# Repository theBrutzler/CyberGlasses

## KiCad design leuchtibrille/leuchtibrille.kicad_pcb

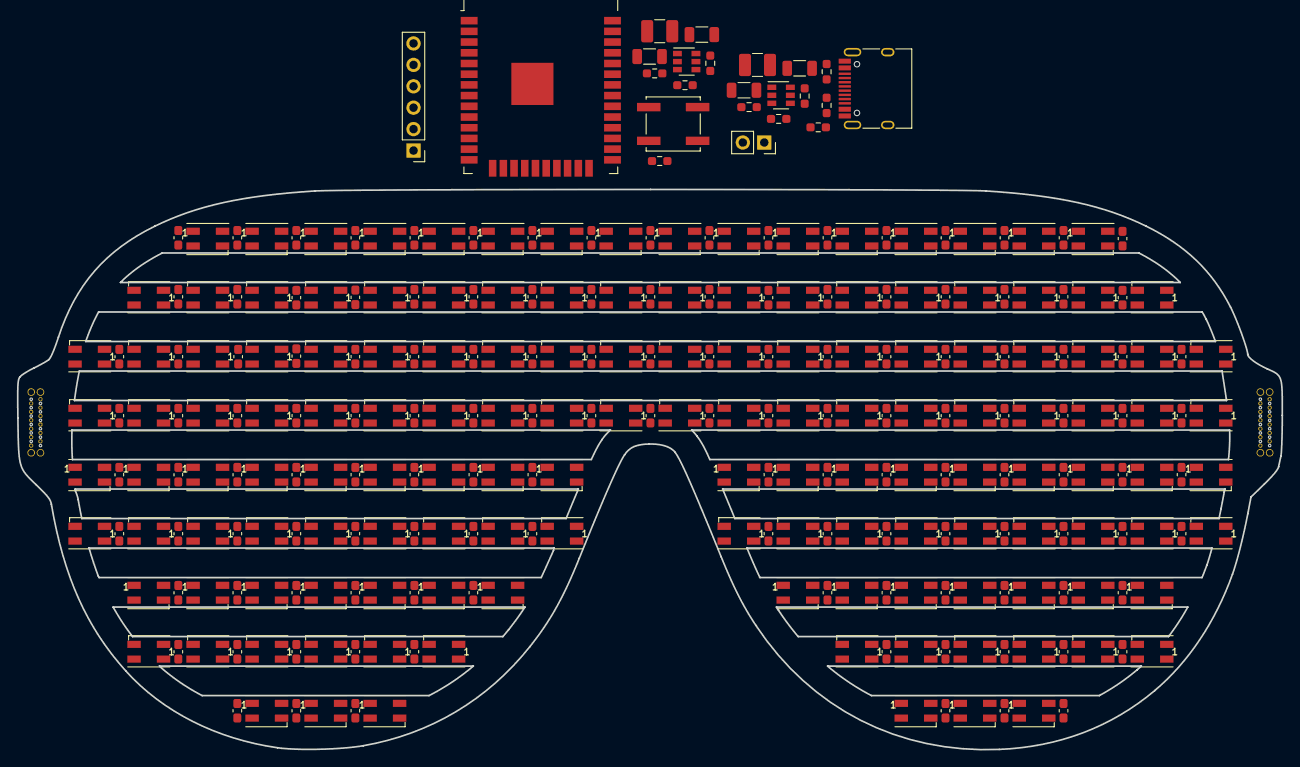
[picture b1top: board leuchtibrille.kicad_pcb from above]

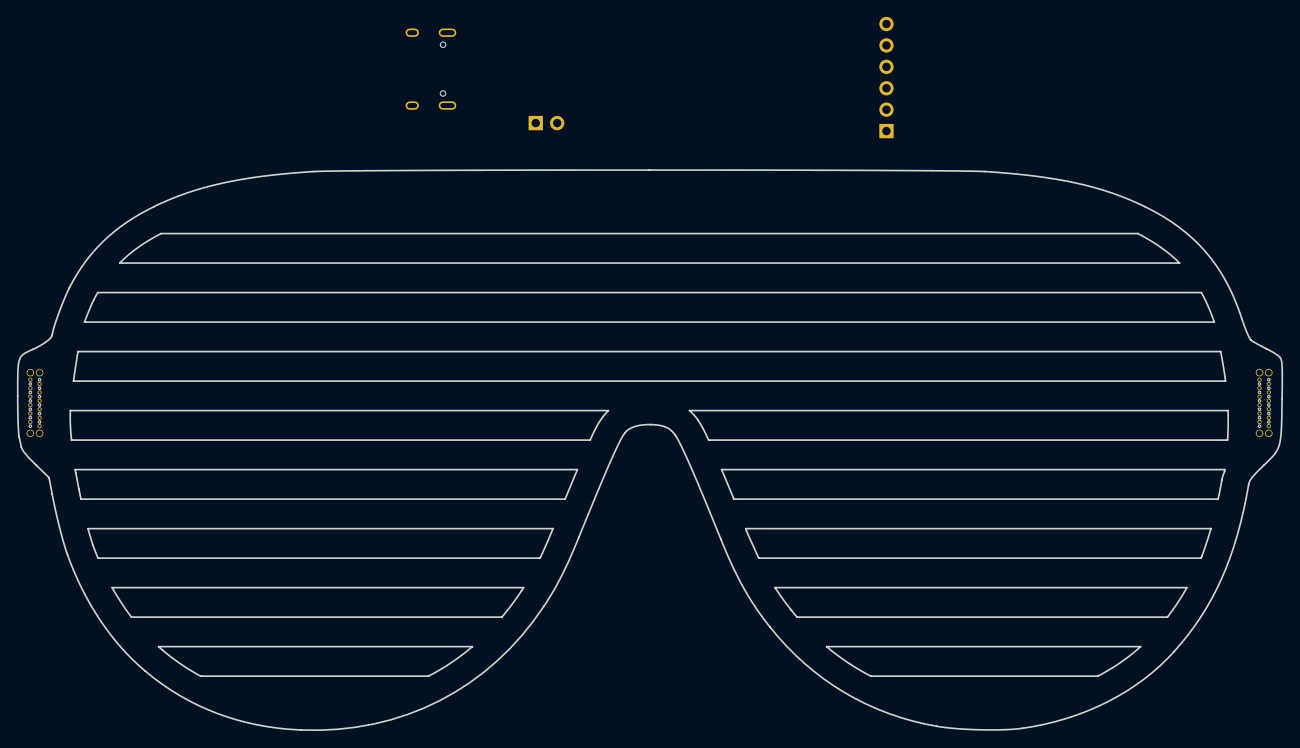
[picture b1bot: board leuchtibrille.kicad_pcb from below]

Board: 2 copper layers, 150.0 x 66.4 mm, 299 parts (2 on the bottom side), 160 nets, no tracks yet.

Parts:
C1, C2, C3, C4: 4µ7; C_1206_3216Metric
C8, C9, C10, C12, C13, C14, C15, C16, C17, C18, C19, C20, C21, C22, C23, C24, C25, C26, C27, C28, C29, C30, C31, C32, C33, C34, C35, C36, C37, C38, C39, C40, C41, C43, C44, C45, C47, C48, C49, C50, C51, C52, C53, C54, C55, C56, C57, C58, C59, C60, C61, C62, C63, C64, C65, C66, C67, C68, C69, C70, C71, C72, C73, C74, C75, C76, C78, C79, C80, C82, C83, C84, C85, C86, C87, C88, C89, C90, C91, C92, C93, C94, C95, C96, C97, C98, C99, C100, C101, C102, C103, C104, C105, C106, C107, C108, C109, C110, C111, C113, C114, C115, C117, C118, C119, C120, C121, C122, C123, C124, C125, C126, C127, C128, C129, C130, C131, C132, C133, C134, C135, C136, C137, C138, C139, C140, C141, C142, C143, C144, C145, C146: C100n; C_0603_1608Metric_Pad1.08x0.95mm_HandSolder
D1, D2, D3, D4, D5, D6, D7, D8, D9, D10, D11, D12, D13, D14, D15, D16, D17, D18, D19, D20, D21, D22, D23, D24, D25, D26, D27, D28, D29, D30, D31, D32, D33, D34, D35, D36, D37, D38, D39, D40, D41, D42, D43, D44, D45, D46, D47, D48, D49, D50, D51, D52, D53, D54, D55, D56, D57, D58, D59, D60, D61, D62, D63, D64, D65, D66, D67, D68, D69, D70, D71, D72, D73, D74, D75, D76, D77, D78, D79, D80, D81, D82, D83, D84, D85, D86, D87, D88, D89, D90, D91, D92, D93, D94, D95, D96, D97, D98, D99, D100, D101, D102, D103, D104, D105, D106, D107, D108, D109, D110, D111, D112, D113, D114, D115, D116, D117, D118, D119, D120, D121, D122, D123, D124, D125, D126, D127, D128, D129, D130, D131, D132, D133, D134, D135, D136, D137, D138, D139, D140, D141, D142: WS2812B; LED_SK6812MINI_PLCC4_3.5x3.5mm_P1.75mm
J1: Conn_01x06_Male; PinHeader_1x06_P2.54mm_Vertical
J2: Conn_01x02_Female; PinSocket_1x02_P2.54mm_Vertical
J3: USB_C_Receptacle_USB2.0; USB_C_Receptacle_HRO_TYPE-C-31-M-12
J4, J5: USB_C_Receptacle_USB2.0; USBC_THT
L1, L2: 2.2µ; L_1210_3225Metric_Pad1.42x2.65mm_HandSolder
R1, R2, R7, R8, R9, R10: 5K1; R_0603_1608Metric_Pad0.98x0.95mm_HandSolder
R3: 590K; R_0603_1608Metric_Pad0.98x0.95mm_HandSolder
R4, R6: 100K; R_0603_1608Metric_Pad0.98x0.95mm_HandSolder
R5: 430K; R_0603_1608Metric_Pad0.98x0.95mm_HandSolder
SW1: SW_Push; SW_Push_1P1T_NO_CK_KSC7xxJ
U1, U2: MT3420C; SOT-23-6
U3: ESP32-WROOM-32

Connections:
+3V3: C4.1, L2.2, R5.1, R7.1, U3.2 (VDD)
+5V: C1.1, J1.4, J3.A4 (VBUS), J3.A9 (VBUS), J3.B4 (VBUS), J3.B9 (VBUS), R1.2, U1.5 (IN)
+BATT: C2.1, C3.1, C8.1, C9.1, C10.1, C12.1, C13.1, C14.1, C15.1, C16.1, C17.1, C18.1, C19.1, C20.1, C21.1, C22.1, C23.1, C24.1, C25.1, C26.1, C27.1, C28.1, C29.1, C30.1, C31.1, C32.1, C33.1, C34.1, C35.1, C36.1, C37.1, C38.1, C39.1, C40.1, C41.1, C43.1, C44.1, C45.1, C47.1, C48.1, C49.1, C50.1, C51.1, C52.1, C53.1, C54.1, C55.1, C56.1, C57.1, C58.1, C59.1, C60.1, C61.1, C62.1, C63.1, C64.1, C65.1, C66.1, C67.1, C68.1, C69.1, C70.1, C71.1, C72.1, C73.1, C74.1, C75.1, C76.1, C78.1, C79.1, C80.1, C82.1, C83.1, C84.1, C85.1, C86.1, C87.1, C88.1, C89.1, C90.1, C91.1, C92.1, C93.1, C94.1, C95.1, C96.1, C97.1, C98.1, C99.1, C100.1, C101.1, C102.1, C103.1, C104.1, C105.1, C106.1, C107.1, C108.1, C109.1, C110.1, C111.1, C113.1, C114.1, C115.1, C117.1, C118.1, C119.1, C120.1, C121.1, C122.1, C123.1, C124.1, C125.1, C126.1, C127.1, C128.1, C129.1, C130.1, C131.1, C132.1, C133.1, C134.1, C135.1, C136.1, C137.1, C138.1, C139.1, C140.1, C141.1, C142.1, C143.1, C144.1, C145.1, C146.1, D1.1 (VDD), D2.1 (VDD), D3.1 (VDD), D4.1 (VDD), D5.1 (VDD), D6.1 (VDD), D7.1 (VDD), D8.1 (VDD), D9.1 (VDD), D10.1 (VDD), D11.1 (VDD), D12.1 (VDD), D13.1 (VDD), D14.1 (VDD), D15.1 (VDD), D16.1 (VDD), D17.1 (VDD), D18.1 (VDD), D19.1 (VDD), D20.1 (VDD), D21.1 (VDD), D22.1 (VDD), D23.1 (VDD), D24.1 (VDD), D25.1 (VDD), D26.1 (VDD), D27.1 (VDD), D28.1 (VDD), D29.1 (VDD), D30.1 (VDD), D31.1 (VDD), D32.1 (VDD), D33.1 (VDD), D34.1 (VDD), D35.1 (VDD), D36.1 (VDD), D37.1 (VDD), D38.1 (VDD), D39.1 (VDD), D40.1 (VDD), D41.1 (VDD), D42.1 (VDD), D43.1 (VDD), D44.1 (VDD), D45.1 (VDD), D46.1 (VDD), D47.1 (VDD), D48.1 (VDD), D49.1 (VDD), D50.1 (VDD), D51.1 (VDD), D52.1 (VDD), D53.1 (VDD), D54.1 (VDD), D55.1 (VDD), D56.1 (VDD), D57.1 (VDD), D58.1 (VDD), D59.1 (VDD), D60.1 (VDD), D61.1 (VDD), D62.1 (VDD), D63.1 (VDD), D64.1 (VDD), D65.1 (VDD), D66.1 (VDD), D67.1 (VDD), D68.1 (VDD), D69.1 (VDD), D70.1 (VDD), D71.1 (VDD), D72.1 (VDD), D73.1 (VDD), D74.1 (VDD), D75.1 (VDD), D76.1 (VDD), D77.1 (VDD), D78.1 (VDD), D79.1 (VDD), D80.1 (VDD), D81.1 (VDD), D82.1 (VDD), D83.1 (VDD), D84.1 (VDD), D85.1 (VDD), D86.1 (VDD), D87.1 (VDD), D88.1 (VDD), D89.1 (VDD), D90.1 (VDD), D91.1 (VDD), D92.1 (VDD), D93.1 (VDD), D94.1 (VDD), D95.1 (VDD), D96.1 (VDD), D97.1 (VDD), D98.1 (VDD), D99.1 (VDD), D100.1 (VDD), D101.1 (VDD), D102.1 (VDD), D103.1 (VDD), D104.1 (VDD), D105.1 (VDD), D106.1 (VDD), D107.1 (VDD), D108.1 (VDD), D109.1 (VDD), D110.1 (VDD), D111.1 (VDD), D112.1 (VDD), D113.1 (VDD), D114.1 (VDD), D115.1 (VDD), D116.1 (VDD), D117.1 (VDD), D118.1 (VDD), D119.1 (VDD), D120.1 (VDD), D121.1 (VDD), D122.1 (VDD), D123.1 (VDD), D124.1 (VDD), D125.1 (VDD), D126.1 (VDD), D127.1 (VDD), D128.1 (VDD), D129.1 (VDD), D130.1 (VDD), D131.1 (VDD), D132.1 (VDD), D133.1 (VDD), D134.1 (VDD), D135.1 (VDD), D136.1 (VDD), D137.1 (VDD), D138.1 (VDD), D139.1 (VDD), D140.1 (VDD), D141.1 (VDD), D142.1 (VDD), J2.2, J4.A9 (VBUS), J4.B4 (VBUS), J5.A4 (VBUS), J5.A9 (VBUS), L1.2, R2.2, R3.1, U2.5 (IN)
/ENABLE: J1.6, U3.3 (EN)
/gschau/DIN: D3.4 (DIN), J5.A6 (D+), J5.A7 (D-)
/gschau/DOUT: D22.2 (DOUT), D38.4 (DIN)
/sheet60A4741D/DOUT: D92.2 (DOUT), D108.4 (DIN)
/sheet60A47726/DOUT: D1.4 (DIN), D127.2 (DOUT)
/sheet60813E03/DOUT: D57.2 (DOUT), D73.4 (DIN)
GND: C1.2, C2.2, C3.2, C4.2, C8.2, C9.2, C10.2, C12.2, C13.2, C14.2, C15.2, C16.2, C17.2, C18.2, C19.2, C20.2, C21.2, C22.2, C23.2, C24.2, C25.2, C26.2, C27.2, C28.2, C29.2, C30.2, C31.2, C32.2, C33.2, C34.2, C35.2, C36.2, C37.2, C38.2, C39.2, C40.2, C41.2, C43.2, C44.2, C45.2, C47.2, C48.2, C49.2, C50.2, C51.2, C52.2, C53.2, C54.2, C55.2, C56.2, C57.2, C58.2, C59.2, C60.2, C61.2, C62.2, C63.2, C64.2, C65.2, C66.2, C67.2, C68.2, C69.2, C70.2, C71.2, C72.2, C73.2, C74.2, C75.2, C76.2, C78.2, C79.2, C80.2, C82.2, C83.2, C84.2, C85.2, C86.2, C87.2, C88.2, C89.2, C90.2, C91.2, C92.2, C93.2, C94.2, C95.2, C96.2, C97.2, C98.2, C99.2, C100.2, C101.2, C102.2, C103.2, C104.2, C105.2, C106.2, C107.2, C108.2, C109.2, C110.2, C111.2, C113.2, C114.2, C115.2, C117.2, C118.2, C119.2, C120.2, C121.2, C122.2, C123.2, C124.2, C125.2, C126.2, C127.2, C128.2, C129.2, C130.2, C131.2, C132.2, C133.2, C134.2, C135.2, C136.2, C137.2, C138.2, C139.2, C140.2, C141.2, C142.2, C143.2, C144.2, C145.2, C146.2, D1.3 (VSS), D2.3 (VSS), D3.3 (VSS), D4.3 (VSS), D5.3 (VSS), D6.3 (VSS), D7.3 (VSS), D8.3 (VSS), D9.3 (VSS), D10.3 (VSS), D11.3 (VSS), D12.3 (VSS), D13.3 (VSS), D14.3 (VSS), D15.3 (VSS), D16.3 (VSS), D17.3 (VSS), D18.3 (VSS), D19.3 (VSS), D20.3 (VSS), D21.3 (VSS), D22.3 (VSS), D23.3 (VSS), D24.3 (VSS), D25.3 (VSS), D26.3 (VSS), D27.3 (VSS), D28.3 (VSS), D29.3 (VSS), D30.3 (VSS), D31.3 (VSS), D32.3 (VSS), D33.3 (VSS), D34.3 (VSS), D35.3 (VSS), D36.3 (VSS), D37.3 (VSS), D38.3 (VSS), D39.3 (VSS), D40.3 (VSS), D41.3 (VSS), D42.3 (VSS), D43.3 (VSS), D44.3 (VSS), D45.3 (VSS), D46.3 (VSS), D47.3 (VSS), D48.3 (VSS), D49.3 (VSS), D50.3 (VSS), D51.3 (VSS), D52.3 (VSS), D53.3 (VSS), D54.3 (VSS), D55.3 (VSS), D56.3 (VSS), D57.3 (VSS), D58.3 (VSS), D59.3 (VSS), D60.3 (VSS), D61.3 (VSS), D62.3 (VSS), D63.3 (VSS), D64.3 (VSS), D65.3 (VSS), D66.3 (VSS), D67.3 (VSS), D68.3 (VSS), D69.3 (VSS), D70.3 (VSS), D71.3 (VSS), D72.3 (VSS), D73.3 (VSS), D74.3 (VSS), D75.3 (VSS), D76.3 (VSS), D77.3 (VSS), D78.3 (VSS), D79.3 (VSS), D80.3 (VSS), D81.3 (VSS), D82.3 (VSS), D83.3 (VSS), D84.3 (VSS), D85.3 (VSS), D86.3 (VSS), D87.3 (VSS), D88.3 (VSS), D89.3 (VSS), D90.3 (VSS), D91.3 (VSS), D92.3 (VSS), D93.3 (VSS), D94.3 (VSS), D95.3 (VSS), D96.3 (VSS), D97.3 (VSS), D98.3 (VSS), D99.3 (VSS), D100.3 (VSS), D101.3 (VSS), D102.3 (VSS), D103.3 (VSS), D104.3 (VSS), D105.3 (VSS), D106.3 (VSS), D107.3 (VSS), D108.3 (VSS), D109.3 (VSS), D110.3 (VSS), D111.3 (VSS), D112.3 (VSS), D113.3 (VSS), D114.3 (VSS), D115.3 (VSS), D116.3 (VSS), D117.3 (VSS), D118.3 (VSS), D119.3 (VSS), D120.3 (VSS), D121.3 (VSS), D122.3 (VSS), D123.3 (VSS), D124.3 (VSS), D125.3 (VSS), D126.3 (VSS), D127.3 (VSS), D128.3 (VSS), D129.3 (VSS), D130.3 (VSS), D131.3 (VSS), D132.3 (VSS), D133.3 (VSS), D134.3 (VSS), D135.3 (VSS), D136.3 (VSS), D137.3 (VSS), D138.3 (VSS), D139.3 (VSS), D140.3 (VSS), D141.3 (VSS), D142.3 (VSS), J1.1, J2.1, J3.A1 (GND), J3.A12 (GND), J3.B1 (GND), J3.B12 (GND), J3.S1 (SHIELD), J4.A1 (GND), J4.B12 (GND), J4.S1 (SHIELD), J5.A12 (GND), J5.B12 (GND), J5.S1 (SHIELD), R4.2, R6.2, R8.1, R9.1, SW1.2, U1.2 (GND), U2.2 (GND), U3.1 (GND), U3.15 (GND), U3.38 (GND), U3.39 (GND)
unnamed: D1.2 (DOUT), D2.4 (DIN)
unnamed: D3.2 (DOUT), D7.4 (DIN)
unnamed: D4.2 (DOUT), D8.4 (DIN)
unnamed: D5.2 (DOUT), D9.4 (DIN)
unnamed: D10.2 (DOUT), D14.4 (DIN)
unnamed: D6.2 (DOUT), D10.4 (DIN)
unnamed: D11.2 (DOUT), D15.4 (DIN)
unnamed: D7.2 (DOUT), D11.4 (DIN)
unnamed: D12.2 (DOUT), D16.4 (DIN)
unnamed: D8.2 (DOUT), D12.4 (DIN)
unnamed: D13.2 (DOUT), D17.4 (DIN)
unnamed: D9.2 (DOUT), D13.4 (DIN)
unnamed: D14.2 (DOUT), D18.4 (DIN)
unnamed: D15.2 (DOUT), D19.4 (DIN)
unnamed: D16.2 (DOUT), D20.4 (DIN)
unnamed: D17.2 (DOUT), D21.4 (DIN)
unnamed: D18.2 (DOUT), D22.4 (DIN)
unnamed: D19.2 (DOUT), D23.4 (DIN)
unnamed: D20.2 (DOUT), D24.4 (DIN)
unnamed: D21.2 (DOUT), D25.4 (DIN)
unnamed: D23.2 (DOUT), D26.4 (DIN)
unnamed: D24.2 (DOUT), D27.4 (DIN)
unnamed: D25.2 (DOUT), D28.4 (DIN)
unnamed: D26.2 (DOUT), D29.4 (DIN)
unnamed: D27.2 (DOUT), D30.4 (DIN)
unnamed: D28.2 (DOUT), D31.4 (DIN)
unnamed: D29.2 (DOUT), D32.4 (DIN)
unnamed: D30.2 (DOUT), D33.4 (DIN)
unnamed: D31.2 (DOUT), D34.4 (DIN)
unnamed: D32.2 (DOUT), D35.4 (DIN)
unnamed: D33.2 (DOUT), D36.4 (DIN)
unnamed: D34.2 (DOUT), D37.4 (DIN)
unnamed: D4.4 (DIN), D35.2 (DOUT)
unnamed: D5.4 (DIN), D36.2 (DOUT)
unnamed: D6.4 (DIN), D37.2 (DOUT)
unnamed: D38.2 (DOUT), D42.4 (DIN)
unnamed: D39.2 (DOUT), D43.4 (DIN)
unnamed: D39.4 (DIN), D70.2 (DOUT)
unnamed: D40.2 (DOUT), D44.4 (DIN)
unnamed: D40.4 (DIN), D71.2 (DOUT)
unnamed: D41.2 (DOUT), D45.4 (DIN)
unnamed: D41.4 (DIN), D72.2 (DOUT)
unnamed: D42.2 (DOUT), D46.4 (DIN)
unnamed: D43.2 (DOUT), D47.4 (DIN)
unnamed: D44.2 (DOUT), D48.4 (DIN)
unnamed: D45.2 (DOUT), D49.4 (DIN)
unnamed: D46.2 (DOUT), D50.4 (DIN)
unnamed: D47.2 (DOUT), D51.4 (DIN)
unnamed: D48.2 (DOUT), D52.4 (DIN)
unnamed: D49.2 (DOUT), D53.4 (DIN)
unnamed: D50.2 (DOUT), D54.4 (DIN)
unnamed: D51.2 (DOUT), D55.4 (DIN)
unnamed: D52.2 (DOUT), D56.4 (DIN)
unnamed: D53.2 (DOUT), D57.4 (DIN)
unnamed: D54.2 (DOUT), D58.4 (DIN)
unnamed: D55.2 (DOUT), D59.4 (DIN)
unnamed: D56.2 (DOUT), D60.4 (DIN)
unnamed: D58.2 (DOUT), D61.4 (DIN)
unnamed: D59.2 (DOUT), D62.4 (DIN)
unnamed: D60.2 (DOUT), D63.4 (DIN)
unnamed: D61.2 (DOUT), D64.4 (DIN)
unnamed: D62.2 (DOUT), D65.4 (DIN)
unnamed: D63.2 (DOUT), D66.4 (DIN)
unnamed: D64.2 (DOUT), D67.4 (DIN)
unnamed: D65.2 (DOUT), D68.4 (DIN)
unnamed: D66.2 (DOUT), D69.4 (DIN)
unnamed: D67.2 (DOUT), D70.4 (DIN)
unnamed: D68.2 (DOUT), D71.4 (DIN)
unnamed: D69.2 (DOUT), D72.4 (DIN)
unnamed: D73.2 (DOUT), D77.4 (DIN)
unnamed: D74.2 (DOUT), D78.4 (DIN)
unnamed: D75.2 (DOUT), D79.4 (DIN)
unnamed: D76.2 (DOUT), D80.4 (DIN)
unnamed: D77.2 (DOUT), D81.4 (DIN)
unnamed: D78.2 (DOUT), D82.4 (DIN)
unnamed: D79.2 (DOUT), D83.4 (DIN)
unnamed: D80.2 (DOUT), D84.4 (DIN)
unnamed: D81.2 (DOUT), D85.4 (DIN)
unnamed: D82.2 (DOUT), D86.4 (DIN)
unnamed: D83.2 (DOUT), D87.4 (DIN)
unnamed: D84.2 (DOUT), D88.4 (DIN)
unnamed: D85.2 (DOUT), D89.4 (DIN)
unnamed: D86.2 (DOUT), D90.4 (DIN)
unnamed: D87.2 (DOUT), D91.4 (DIN)
unnamed: D88.2 (DOUT), D92.4 (DIN)
unnamed: D89.2 (DOUT), D93.4 (DIN)
unnamed: D90.2 (DOUT), D94.4 (DIN)
unnamed: D91.2 (DOUT), D95.4 (DIN)
unnamed: D93.2 (DOUT), D96.4 (DIN)
unnamed: D94.2 (DOUT), D97.4 (DIN)
unnamed: D95.2 (DOUT), D98.4 (DIN)
unnamed: D96.2 (DOUT), D99.4 (DIN)
unnamed: D100.2 (DOUT), D103.4 (DIN)
unnamed: D97.2 (DOUT), D100.4 (DIN)
unnamed: D101.2 (DOUT), D104.4 (DIN)
unnamed: D98.2 (DOUT), D101.4 (DIN)
unnamed: D102.2 (DOUT), D105.4 (DIN)
unnamed: D99.2 (DOUT), D102.4 (DIN)
unnamed: D103.2 (DOUT), D106.4 (DIN)
unnamed: D104.2 (DOUT), D107.4 (DIN)
unnamed: D74.4 (DIN), D105.2 (DOUT)
unnamed: D75.4 (DIN), D106.2 (DOUT)
unnamed: D76.4 (DIN), D107.2 (DOUT)
unnamed: D108.2 (DOUT), D112.4 (DIN)
unnamed: D109.2 (DOUT), D113.4 (DIN)
unnamed: D109.4 (DIN), D140.2 (DOUT)
unnamed: D110.2 (DOUT), D114.4 (DIN)
unnamed: D110.4 (DIN), D141.2 (DOUT)
unnamed: D111.2 (DOUT), D115.4 (DIN)
unnamed: D111.4 (DIN), D142.2 (DOUT)
unnamed: D112.2 (DOUT), D116.4 (DIN)
unnamed: D113.2 (DOUT), D117.4 (DIN)
unnamed: D114.2 (DOUT), D118.4 (DIN)
unnamed: D115.2 (DOUT), D119.4 (DIN)
unnamed: D116.2 (DOUT), D120.4 (DIN)
unnamed: D117.2 (DOUT), D121.4 (DIN)
unnamed: D118.2 (DOUT), D122.4 (DIN)
unnamed: D119.2 (DOUT), D123.4 (DIN)
unnamed: D120.2 (DOUT), D124.4 (DIN)
unnamed: D121.2 (DOUT), D125.4 (DIN)
unnamed: D122.2 (DOUT), D126.4 (DIN)
unnamed: D123.2 (DOUT), D127.4 (DIN)
unnamed: D124.2 (DOUT), D128.4 (DIN)
unnamed: D125.2 (DOUT), D129.4 (DIN)
unnamed: D126.2 (DOUT), D130.4 (DIN)
unnamed: D128.2 (DOUT), D131.4 (DIN)
unnamed: D129.2 (DOUT), D132.4 (DIN)
unnamed: D130.2 (DOUT), D133.4 (DIN)
unnamed: D131.2 (DOUT), D134.4 (DIN)
unnamed: D132.2 (DOUT), D135.4 (DIN)
unnamed: D133.2 (DOUT), D136.4 (DIN)
unnamed: D134.2 (DOUT), D137.4 (DIN)
unnamed: D135.2 (DOUT), D138.4 (DIN)
unnamed: D136.2 (DOUT), D139.4 (DIN)
unnamed: D137.2 (DOUT), D140.4 (DIN)
unnamed: D138.2 (DOUT), D141.4 (DIN)
unnamed: D139.2 (DOUT), D142.4 (DIN)
unnamed: J1.2, U3.34 (RXD0/IO3)
unnamed: J1.3, U3.35 (TXD0/IO1)
unnamed: J1.5, R7.2, SW1.1, U3.25 (IO0)
unnamed: J3.A5 (CC1), R8.2
unnamed: J3.A6 (D+), R10.2
unnamed: J3.B5 (CC2), R9.2
unnamed: L1.1, U1.1 (SW)
unnamed: L2.1, U2.1 (SW)
unnamed: R1.1, U1.4 (EN)
unnamed: R2.1, U2.4 (EN)
unnamed: R3.2, R4.1, U1.3 (FB)
unnamed: R5.2, R6.1, U2.3 (FB)
unnamed: R10.1, U3.24 (IO2)

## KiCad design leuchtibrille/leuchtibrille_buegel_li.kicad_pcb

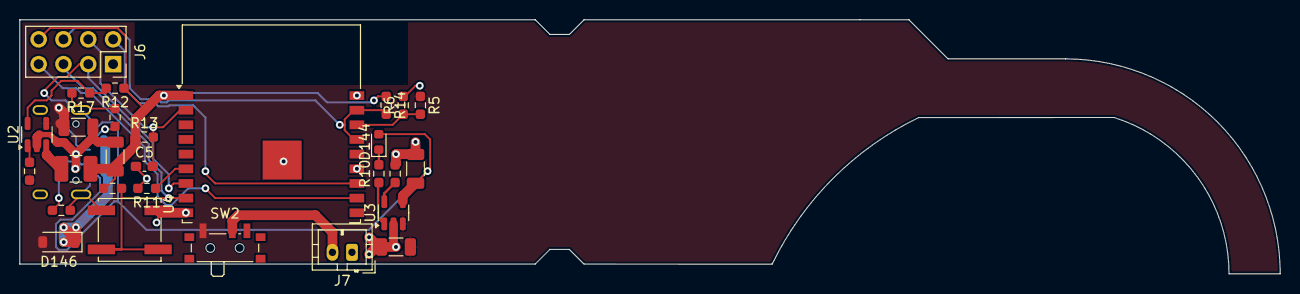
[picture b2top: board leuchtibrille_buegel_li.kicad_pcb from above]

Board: 2 copper layers, 129.0 x 26.0 mm, 29 parts (1 on the bottom side), 22 nets.

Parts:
C1, C2, C3, C4: 4µ7; C_1206_3216Metric
C5: C100n; C_0603_1608Metric_Pad1.08x0.95mm_HandSolder
D144: LED; LED_0603_1608Metric
D146: MBR0520; D_SOD-123
J3: USB_C_Receptacle_USB2.0; USB_C_Receptacle_HRO_TYPE-C-31-M-12
J6: Conn_02x04_Odd_Even; PinSocket_2x04_P2.54mm_Vertical
J7: Conn_01x02_Female; JST_PH_B2B-PH-K_1x02_P2.00mm_Vertical
L2: 2.2µ; L_1210_3225Metric_Pad1.42x2.65mm_HandSolder
R1, R2, R7, R8, R9, R10, R11, R13, R14: 5K1; R_0603_1608Metric_Pad0.98x0.95mm_HandSolder
R5, R12: 430K; R_0603_1608Metric_Pad0.98x0.95mm_HandSolder
R6, R17: 100K; R_0603_1608Metric_Pad0.98x0.95mm_HandSolder
SW1: SW_Push; SW_Push_1P1T_NO_CK_KSC7xxJ
SW2: SW_DIP_x01; SW_SPDT_PCM12
U2: XM5062S; SOT-23-5
U3: MCP73831-2-OT; SOT-23-5
U4: ESP-WROOM-02

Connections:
+3V3: C4.1, J6.8, L2.2, R7.1, R12.1, R13.1, R14.1, U4.1 (VDD)
+5V: C1.1, D144.2 (A), J3.A4 (VBUS), J3.A9 (VBUS), J3.B4 (VBUS), J3.B9 (VBUS), U3.4 (V_{DD})
+BATT: C2.1, C3.1, D146.2 (A), R2.2, R5.1, SW2.1, U2.4 (VIN), U3.3 (V_{BAT})
/ENABLE: C5.2, J6.4, R13.2, U4.2 (EN)
/RST: J6.6, R14.2, U4.15 (RST), U4.17 (IO16)
/RX: J6.7, U4.11 (RXD)
/TX: J6.2, U4.12 (TXD)
/VBAT_ADC: R5.2, R6.1, U4.16 (TOUT)
GND: C1.2, C2.2, C3.2, C4.2, C5.1, J3.A1 (GND), J3.A12 (GND), J3.B1 (GND), J3.B12 (GND), J3.S1 (SHIELD), J6.1, J7.1, R1.2, R6.2, R8.1, R9.1, R11.2, R17.2, SW1.2, U2.2 (GND), U3.2 (V_{SS}), U4.9 (GND), U4.13 (GND), U4.18 (GND), U4.19 (GND)
unnamed: D144.1 (K), R10.2
unnamed: D146.1 (K), J3.A8 (SBU1), J3.B8 (SBU2)
unnamed: J3.A5 (CC1), R8.2
unnamed: J3.B5 (CC2), R9.2
unnamed: J3.A7 (D-), J6.3, U4.7 (IO2)
unnamed: J6.5, R7.2, SW1.1, U4.8 (IO0)
unnamed: J7.2, SW2.2
unnamed: R2.1, U2.1 (EN)
unnamed: R12.2, R17.1, U2.5 (FB)
unnamed: L2.1, U2.3 (SW)
unnamed: R1.1, U3.5 (PROG)
unnamed: R10.1, U3.1 (STAT)
unnamed: R11.1, U4.6 (IO15)

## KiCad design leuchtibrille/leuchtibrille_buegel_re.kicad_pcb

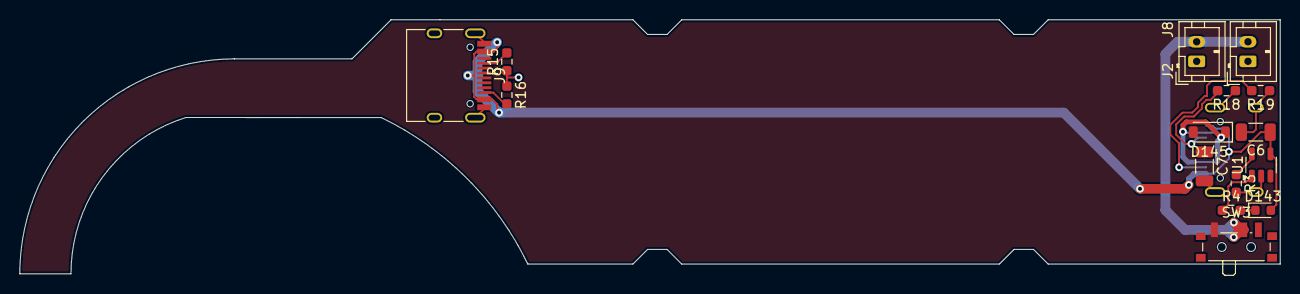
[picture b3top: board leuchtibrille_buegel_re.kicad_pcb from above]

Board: 2 copper layers, 129.0 x 26.0 mm, 16 parts (1 on the bottom side), 12 nets.

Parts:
C6, C7: 4µ7; C_1206_3216Metric
D143: LED; LED_0603_1608Metric
D145: MBR0520; D_SOD-123
J1, J9: USB_C_Receptacle_USB2.0; USB_C_Receptacle_HRO_TYPE-C-31-M-12
J2, J8: Conn_01x02_Female; JST_PH_B2B-PH-K_1x02_P2.00mm_Vertical
R3, R4, R15, R16, R18, R19: 5K1; R_0603_1608Metric_Pad0.98x0.95mm_HandSolder
SW3: SW_DIP_x01; SW_SPDT_PCM12
U1: MCP73831-2-OT; SOT-23-5

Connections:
+5V: C6.1, D143.2 (A), J1.A4 (VBUS), J1.A9 (VBUS), J1.B4 (VBUS), J1.B9 (VBUS), J9.A4 (VBUS), J9.A9 (VBUS), J9.B4 (VBUS), J9.B9 (VBUS), U1.4 (V_{DD})
+BATT: C7.1, D145.2 (A), SW3.1, U1.3 (V_{BAT})
GND: C6.2, C7.2, J1.A1 (GND), J1.A12 (GND), J1.B1 (GND), J1.B12 (GND), J1.S1 (SHIELD), J2.1, J8.1, J9.A1 (GND), J9.A12 (GND), J9.B1 (GND), J9.B12 (GND), J9.S1 (SHIELD), R3.2, R15.1, R16.1, R18.1, R19.1, U1.2 (V_{SS})
unnamed: D143.1 (K), R4.2
unnamed: D145.1 (K), J1.A8 (SBU1), J1.B8 (SBU2)
unnamed: J1.A5 (CC1), R18.2
unnamed: J1.B5 (CC2), R19.2
unnamed: J2.2, J8.2, SW3.2
unnamed: J9.A5 (CC1), R15.2
unnamed: J9.B5 (CC2), R16.2
unnamed: R3.1, U1.5 (PROG)
unnamed: R4.1, U1.1 (STAT)

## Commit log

2021-06-25 Initial Placing
    Rooting is missin
2024-04-18 Upload of working version
